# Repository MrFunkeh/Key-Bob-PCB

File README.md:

# Key Bob

Key Bob is a small cube that you use to interact with other Key Bob's

This project was inspired by the tomagotchi and the STARBIE, I wanted to make something somewhat in between the two but with more capabilities and in a small package.

----------------------------------------------------------------------------------------------------------------------------------------------

Why I built it
----------------

I built this for the week one of Hack Clucb Half Life Event.

I wanted a fun complex build that was new.

Features
----------
- Simple single color OLED display
- One button and rotation of an encoder/ knob input
- Battery Powerd
- USB C charging

  What I learned
  ----------------
  - C++ coding
  - Kicad software
  - Documenting
  - Creating BOM
  - Time management

----------------------------------------------------------------------------------------------------------------------------------------------

  Project Status
  ---------------
  
Work In Progress (just needs updated code in future)

- Gyro to detect movement
- Multipule characters
- Dance in sync with another Key Bob

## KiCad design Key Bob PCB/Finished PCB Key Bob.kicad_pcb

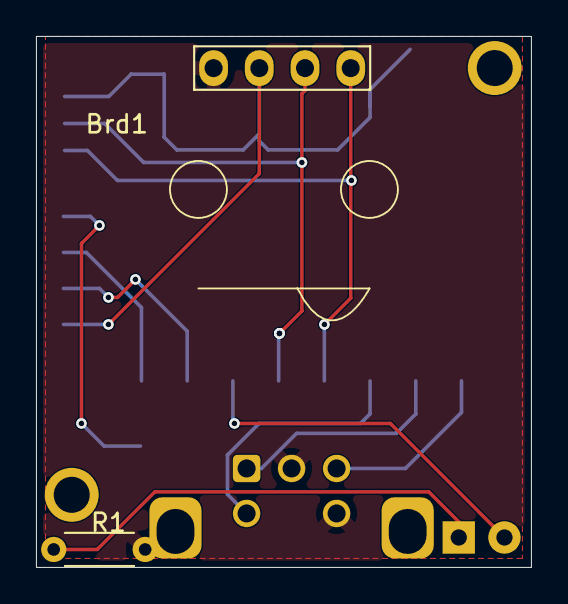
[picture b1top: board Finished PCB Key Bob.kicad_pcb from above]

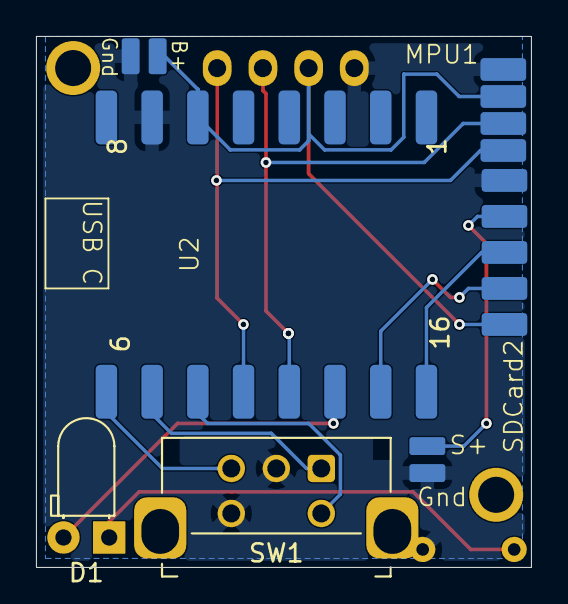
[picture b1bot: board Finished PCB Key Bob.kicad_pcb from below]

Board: 2 copper layers, 27.5 x 29.5 mm, 9 parts (7 on the bottom side), 12 nets.

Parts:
Brd1: SSD1306; 128x64OLED
D1: LED; LED_D3.0mm_Horizontal_O1.27mm_Z2.0mm
LS1: Speaker; Input
MPU1: MPU6050
R1: R; R_Axial_DIN0204_L3.6mm_D1.6mm_P5.08mm_Horizontal
SDCard2: SD Card
SW1: RotaryEncoder_Switch; RotaryEncoder_Bourns_Horizontal_PEC12R-2x17F-Sxxxx
U1: Input
U2: ESP32-C3-SuperMini

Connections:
+3.3V: Brd1.2 (VCC), MPU1.1 (VCC), SDCard2.1 (Vcc), U1.1 (B+), U2.6 (3V3)
/GPIO5: SW1.B, U2.9 (GPIO5)
/GPIO6: SW1.A, U2.10 (GPIO6)
/GPIO7: SW1.S1, U2.11 (GPIO7)
/GPIO8/SDA: Brd1.4 (SDA), MPU1.4 (SDA), U2.12 (GPIO8)
/GPIO9/SCL: Brd1.3 (SCL), MPU1.3 (SCL), U2.13 (GPIO9)
/GPIO10: D1.2 (A), U2.14 (GPIO10)
/GPIO20/RX: SDCard2.2 (RX), U2.15 (GPIO20)
/GPIO21/TX: SDCard2.3 (TX), U2.16 (GPIO21)
/SPK_1: LS1.1, SDCard2.6 (SPK_1)
GND: Brd1.1 (GND), LS1.2, MPU1.2 (GND), R1.1, SDCard2.7 (GND), SW1.C, SW1.S2, U1.2 (Gnd), U2.7 (GND)
unnamed: D1.1 (K), R1.2
